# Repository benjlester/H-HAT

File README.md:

# DAQ Hat (H-HAT) for MCC128
 
 <div class="row">
  <div class="column">
    
  </div>
  <div class="column">
    
  </div>
  <div class="column">
    
  </div>
</div>

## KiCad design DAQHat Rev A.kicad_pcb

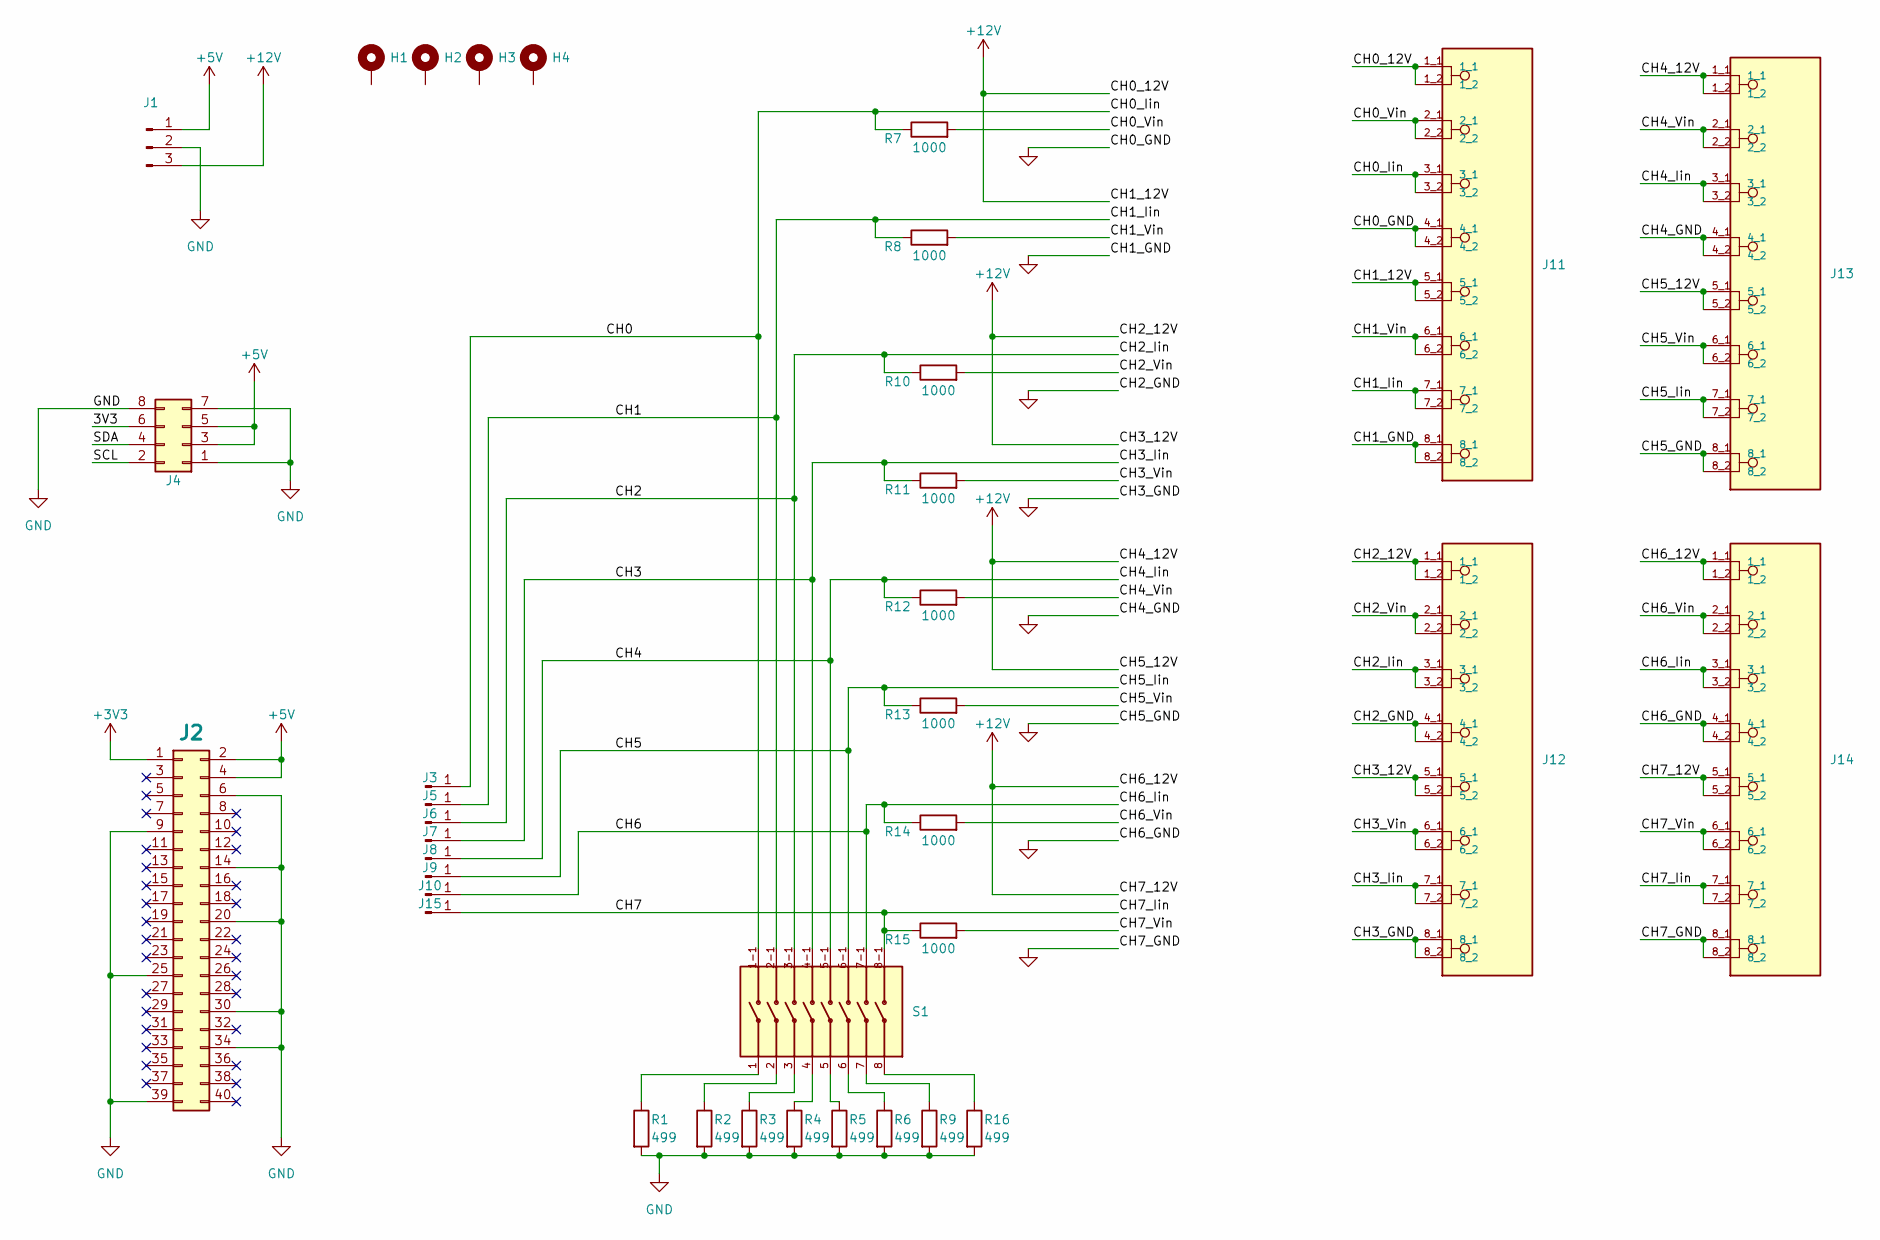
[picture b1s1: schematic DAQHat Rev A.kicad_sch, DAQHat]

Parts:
H1, H2, H3, H4: MountingHole_Pad_MP; MountingHole_2.7mm_M2.5_ISO7380_Pad
J1: MPN U3V16F12
J2: PinSocket_2x20_P2.54mm_Vertical; MPN 61304021821
J3, J5, J6, J7, J8, J9, J10, J15: Conn_01x01_Pin; SolderWire-0.75sqmm_1x01_D1.25mm_OD2.3mm
J4: PinHeader_2x04_P2.54mm_Horizontal; MPN 61300821021
J11, J12, J13, J14: PHOENIX_1862107; MPN 1862107
R1, R2, R3, R4, R5, R6, R9, R16: 499; R_0805_2012Metric_Pad1.20x1.40mm_HandSolder; MPN PHP00805E4990BST1
R7, R8, R10, R11, R12, R13, R14, R15: 1000; R_0805_2012Metric_Pad1.20x1.40mm_HandSolder; MPN RA73F2A1K0BTD
S1: SW_ADE0804; PARTREV R1

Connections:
+3V3: J2.1
+5V: J1.1, J2.2, J2.4, J4.3, J4.5
+12V: J1.3, J11.1_1, J11.1_2, J11.5_1, J11.5_2, J12.1_1, J12.1_2, J12.5_1, J12.5_2, J13.1_1, J13.1_2, J13.5_1, J13.5_2, J14.1_1, J14.1_2, J14.5_1, J14.5_2
/3V3: J4.6
/CH0: J3.1, J11.3_1, J11.3_2, R7.1, S1.1-1
/CH0_Vin: J11.2_1, J11.2_2, R7.2
/CH1: J5.1, J11.7_1, J11.7_2, R8.1, S1.2-1
/CH1_Vin: J11.6_1, J11.6_2, R8.2
/CH2: J6.1, J12.3_1, J12.3_2, R10.1, S1.3-1
/CH2_Vin: J12.2_1, J12.2_2, R10.2
/CH3: J7.1, J12.7_1, J12.7_2, R11.1, S1.4-1
/CH3_Vin: J12.6_1, J12.6_2, R11.2
/CH4: J8.1, J13.3_1, J13.3_2, R12.1, S1.5-1
/CH4_Vin: J13.2_1, J13.2_2, R12.2
/CH5: J9.1, J13.7_1, J13.7_2, R13.1, S1.6-1
/CH5_Vin: J13.6_1, J13.6_2, R13.2
/CH6: J10.1, J14.3_1, J14.3_2, R14.1, S1.7-1
/CH6_Vin: J14.2_1, J14.2_2, R14.2
/CH7: J14.7_1, J14.7_2, J15.1, R15.1, S1.8-1
/CH7_Vin: J14.6_1, J14.6_2, R15.2
/SCL: J4.2
/SDA: J4.4
GND: J1.2, J2.6, J2.9, J2.14, J2.20, J2.25, J2.30, J2.34, J2.39, J4.1, J4.7, J4.8, J11.4_1, J11.4_2, J11.8_1, J11.8_2, J12.4_1, J12.4_2, J12.8_1, J12.8_2, J13.4_1, J13.4_2, J13.8_1, J13.8_2, J14.4_1, J14.4_2, J14.8_1, J14.8_2, R1.2, R2.2, R3.2, R4.2, R5.2, R6.2, R9.2, R16.2
unnamed: R1.1, S1.1
unnamed: R2.1, S1.2
unnamed: R3.1, S1.3
unnamed: R4.1, S1.4
unnamed: R5.1, S1.5
unnamed: R6.1, S1.6
unnamed: R9.1, S1.7
unnamed: R16.1, S1.8

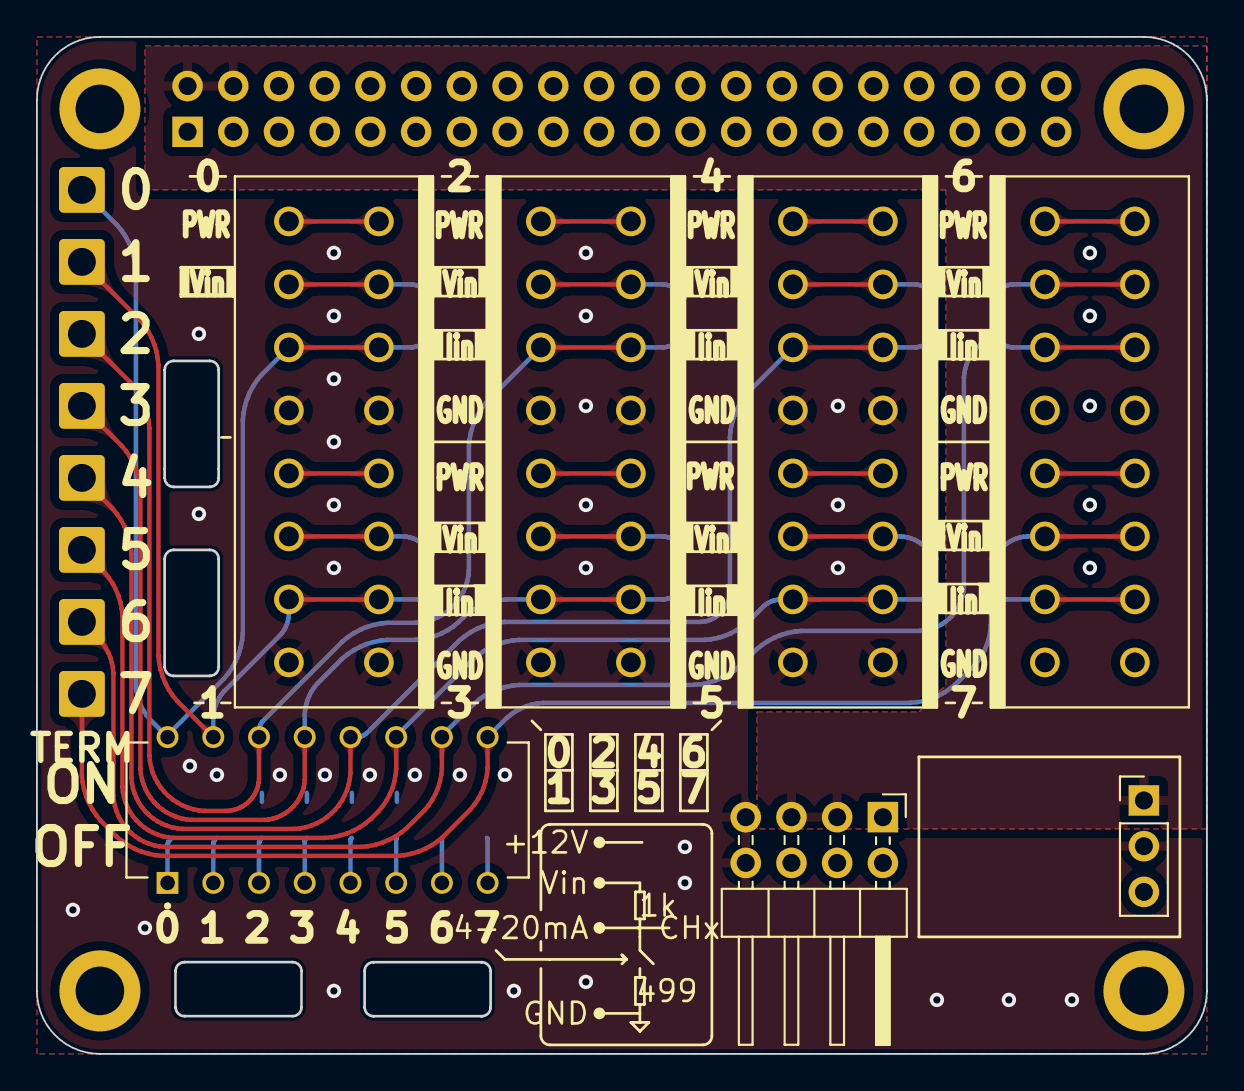
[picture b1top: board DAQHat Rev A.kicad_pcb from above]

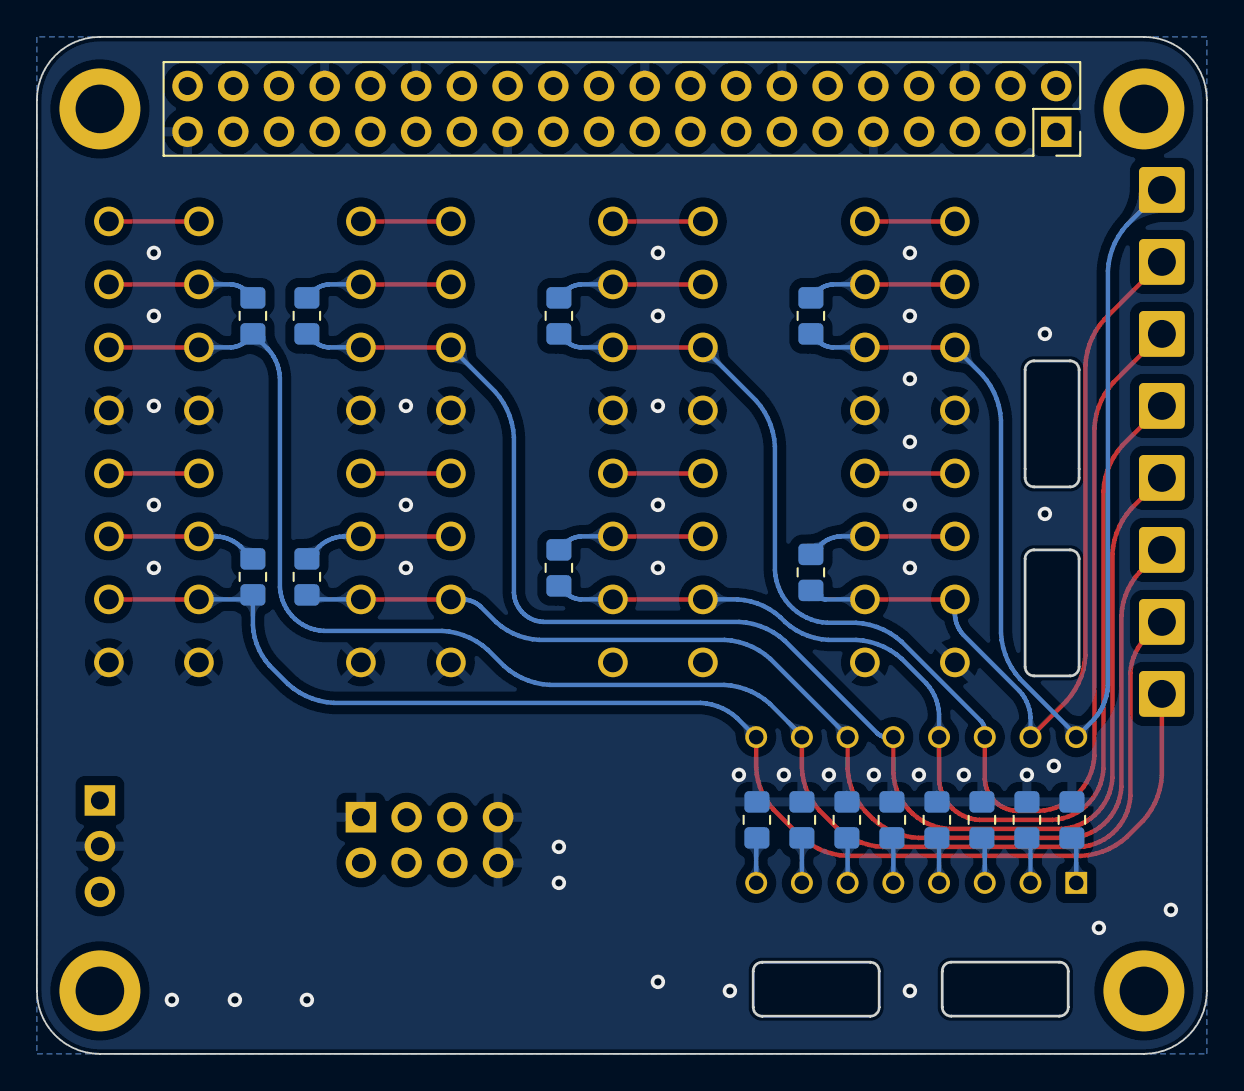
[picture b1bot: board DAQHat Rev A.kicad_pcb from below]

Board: 4 copper layers, 65.0 x 56.4 mm, 36 parts (17 on the bottom side), 27 nets.

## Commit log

2025-05-29 updated gitignore
2025-05-29 removed unused files
2025-05-29 added README
2025-06-18 moved traces and increased standoff distance from polygons to board edge
